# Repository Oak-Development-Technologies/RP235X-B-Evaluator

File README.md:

<image src="Images/RP235X-B_Rendering.png">
# RP235X-B-Evaluator
Open source repository for storing the files for the RP235X-B Evaluator, an RP235X-B Evaluation board.

### Schematic

Here's the first page of the schematic:

<image src="Images/RP235X_FPGA.svg">

### Find the full PDF of the Schematic here:

[PDF Schematic Here](RP235X_FPGA.pdf)

Mind the name of the files, there is plans to eventually add an FPGA add on board for this. Stay tuned! :)

More Coming Soon!

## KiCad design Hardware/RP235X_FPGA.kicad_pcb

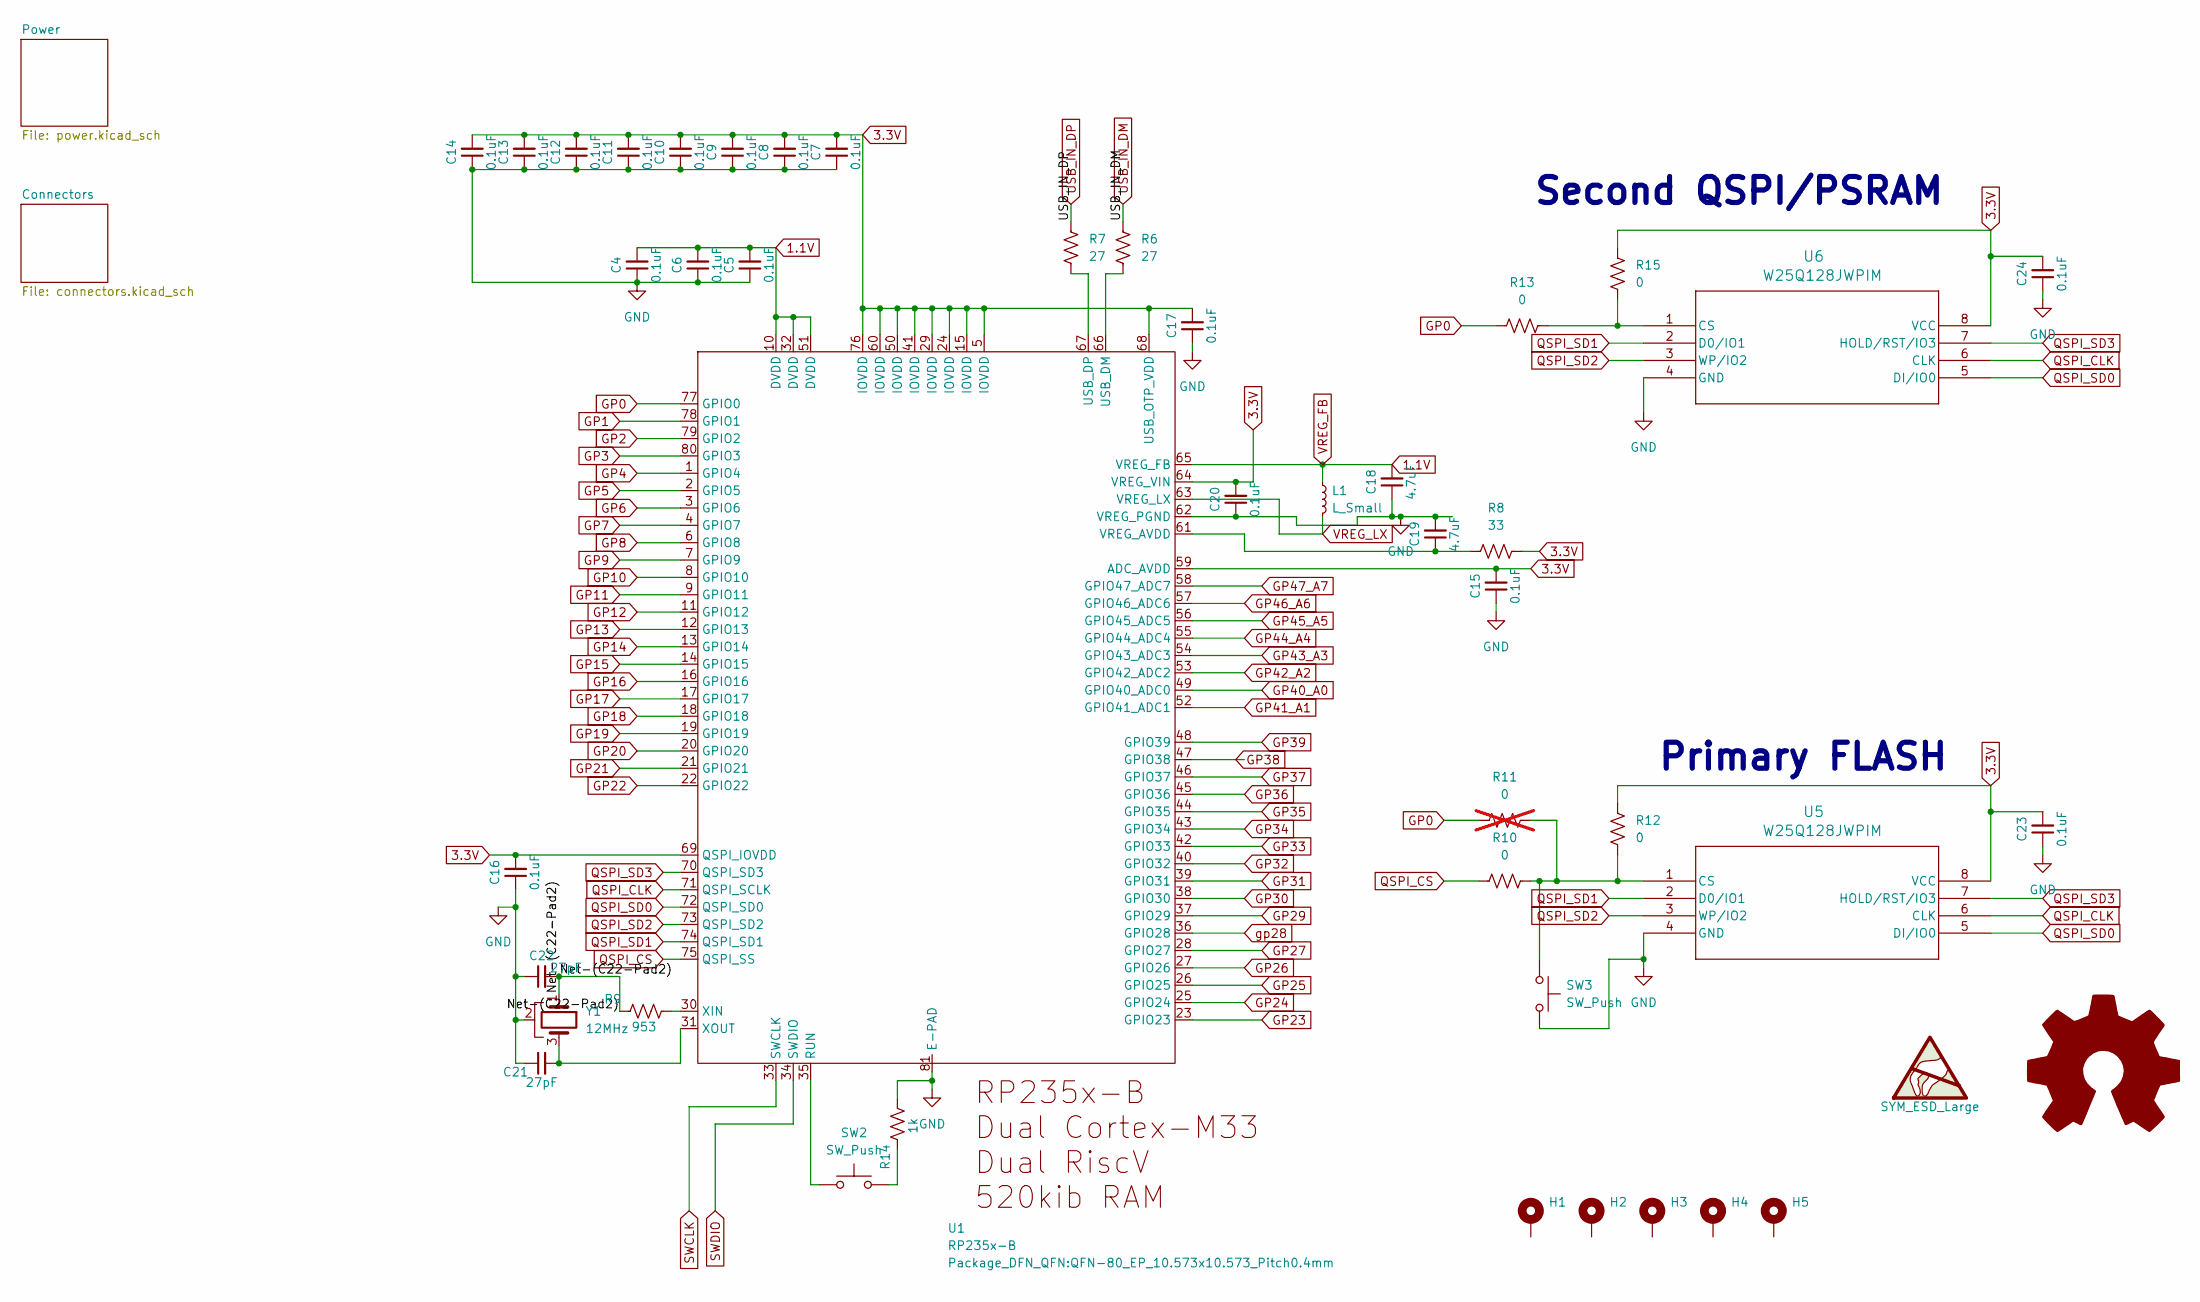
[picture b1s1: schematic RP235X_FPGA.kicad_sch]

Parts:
C4, C5, C6, C7, C8, C9, C10, C11, C12, C13, C14, C15, C16, C17, C20, C23, C24: 0.1uF; C_0402_1005Metric
C18, C19: 4.7uF; C_0402_1005Metric
C21, C22: 27pF; C_0402_1005Metric
H1, H2, H3, H4: MountingHole_Pad; MountingHole_2.5mm_Pad_TopBottom
H5: MountingHole_Pad; KiCad-Logo2_5mm_SilkScreen
L1: L_Small; L_Wurth_WE-LQSH-3012
R6, R7: 27; R_0402_1005Metric
R8: 33; R_0402_1005Metric
R9: 953; R_0402_1005Metric
R10, R12, R13, R15: 0; R_0402_1005Metric
R11: 0; R_0402_1005Metric; not fitted
R14: 1k; R_0402_1005Metric
SW2, SW3: SW_Push; SW_SPST_SKQG_WithStem
U1: RP235x-B; QFN-80_EP_10.573x10.573_Pitch0.4mm
U5, U6: W25Q128JWPIM; W25Q128JW_WSON 6x5-mm_WIN
Y1: 12MHz; Crystal_SMD_SeikoEpson_FA238-4Pin_3.2x2.5mm

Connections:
1.1V: C4.2, C5.2, C6.2, C18.2, L1.1, U1.10 (DVDD), U1.32 (DVDD), U1.51 (DVDD), U1.65 (VREG_FB)
3.3V: C7.2, C8.2, C9.2, C10.2, C11.2, C12.2, C13.2, C14.2, C15.2, C16.2, C17.2, C20.2, C23.2, C24.2, R8.2, R12.2, R15.2, U1.5 (IOVDD), U1.15 (IOVDD), U1.24 (IOVDD), U1.29 (IOVDD), U1.41 (IOVDD), U1.50 (IOVDD), U1.59 (ADC_AVDD), U1.60 (IOVDD), U1.64 (VREG_VIN), U1.68 (USB_OTP_VDD), U1.69 (QSPI_IOVDD), U1.76 (IOVDD), U5.8 (VCC), U6.8 (VCC); also elsewhere on the board
/Net-(C22-Pad2): C22.2, R9.1, Y1.1
GND: C4.1, C5.1, C6.1, C7.1, C8.1, C9.1, C10.1, C11.1, C12.1, C13.1, C14.1, C15.1, C16.1, C17.1, C18.1, C19.2, C20.1, C21.1, C22.1, C23.1, C24.1, R14.2, SW3.2, U1.62 (VREG_PGND), U1.81 (E-PAD), U5.4 (GND), U6.4 (GND), Y1.2; also elsewhere on the board
GP0: R11.1, R13.1, U1.77 (GPIO0); also elsewhere on the board
GP1: U1.78 (GPIO1); also elsewhere on the board
GP2: U1.79 (GPIO2); also elsewhere on the board
GP3: U1.80 (GPIO3); also elsewhere on the board
GP4: U1.1 (GPIO4); also elsewhere on the board
GP5: U1.2 (GPIO5); also elsewhere on the board
GP6: U1.3 (GPIO6); also elsewhere on the board
GP7: U1.4 (GPIO7); also elsewhere on the board
GP8: U1.6 (GPIO8); also elsewhere on the board
GP9: U1.7 (GPIO9); also elsewhere on the board
GP10: U1.8 (GPIO10); also elsewhere on the board
GP11: U1.9 (GPIO11); also elsewhere on the board
GP12: U1.11 (GPIO12); also elsewhere on the board
GP13: U1.12 (GPIO13); also elsewhere on the board
GP14: U1.13 (GPIO14); also elsewhere on the board
GP15: U1.14 (GPIO15); also elsewhere on the board
GP16: U1.16 (GPIO16); also elsewhere on the board
GP17: U1.17 (GPIO17); also elsewhere on the board
GP18: U1.18 (GPIO18); also elsewhere on the board
GP19: U1.19 (GPIO19); also elsewhere on the board
GP20: U1.20 (GPIO20); also elsewhere on the board
GP21: U1.21 (GPIO21); also elsewhere on the board
GP22: U1.22 (GPIO22); also elsewhere on the board
GP23: U1.23 (GPIO23); also elsewhere on the board
GP24: U1.25 (GPIO24); also elsewhere on the board
GP25: U1.26 (GPIO25); also elsewhere on the board
GP26: U1.27 (GPIO26); also elsewhere on the board
GP27: U1.28 (GPIO27); also elsewhere on the board
GP29: U1.37 (GPIO29); also elsewhere on the board
GP30: U1.38 (GPIO30); also elsewhere on the board
GP31: U1.39 (GPIO31); also elsewhere on the board
GP32: U1.40 (GPIO32); also elsewhere on the board
GP33: U1.42 (GPIO33); also elsewhere on the board
GP34: U1.43 (GPIO34); also elsewhere on the board
GP35: U1.44 (GPIO35); also elsewhere on the board
GP36: U1.45 (GPIO36); also elsewhere on the board
GP37: U1.46 (GPIO37); also elsewhere on the board
GP38: U1.47 (GPIO38); also elsewhere on the board
GP39: U1.48 (GPIO39); also elsewhere on the board
GP40_A0: U1.49 (GPIO40_ADC0); also elsewhere on the board
GP41_A1: U1.52 (GPIO41_ADC1); also elsewhere on the board
GP42_A2: U1.53 (GPIO42_ADC2); also elsewhere on the board
GP43_A3: U1.54 (GPIO43_ADC3); also elsewhere on the board
GP44_A4: U1.55 (GPIO44_ADC4); also elsewhere on the board
GP45_A5: U1.56 (GPIO45_ADC5); also elsewhere on the board
GP46_A6: U1.57 (GPIO46_ADC6); also elsewhere on the board
GP47_A7: U1.58 (GPIO47_ADC7); also elsewhere on the board
unnamed: R14.1, SW2.2
unnamed: SW2.1, U1.35 (RUN)
unnamed: R6.2, U1.66 (USB_DM)
unnamed: R7.2, U1.67 (USB_DP)
unnamed: C19.1, R8.1, U1.61 (VREG_AVDD)
unnamed: R9.2, U1.30 (XIN)
unnamed: C21.2, U1.31 (XOUT), Y1.3
unnamed: R10.2, R11.2, R12.1, SW3.1, U5.1 (CS)
unnamed: R13.2, R15.1, U6.1 (CS)
QSPI_CLK: U1.71 (QSPI_SCLK), U5.6 (CLK), U6.6 (CLK)
QSPI_CS: R10.1, U1.75 (QSPI_SS)
QSPI_SD0: U1.72 (QSPI_SD0), U5.5 (DI/IO0), U6.5 (DI/IO0)
QSPI_SD1: U1.74 (QSPI_SD1), U5.2 (D0/IO1), U6.2 (D0/IO1)
QSPI_SD2: U1.73 (QSPI_SD2), U5.3 (WP/IO2), U6.3 (WP/IO2)
QSPI_SD3: U1.70 (QSPI_SD3), U5.7 (HOLD/RST/IO3), U6.7 (HOLD/RST/IO3)
SWCLK: U1.33 (SWCLK); also elsewhere on the board
SWDIO: U1.34 (SWDIO); also elsewhere on the board
USB_IN_DM: R6.1; also elsewhere on the board
USB_IN_DP: R7.1; also elsewhere on the board
VREG_LX: L1.2, U1.63 (VREG_LX)
gp28: U1.36 (GPIO28); also elsewhere on the board

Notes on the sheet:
Second QSPI/PSRAM
Primary FLASH

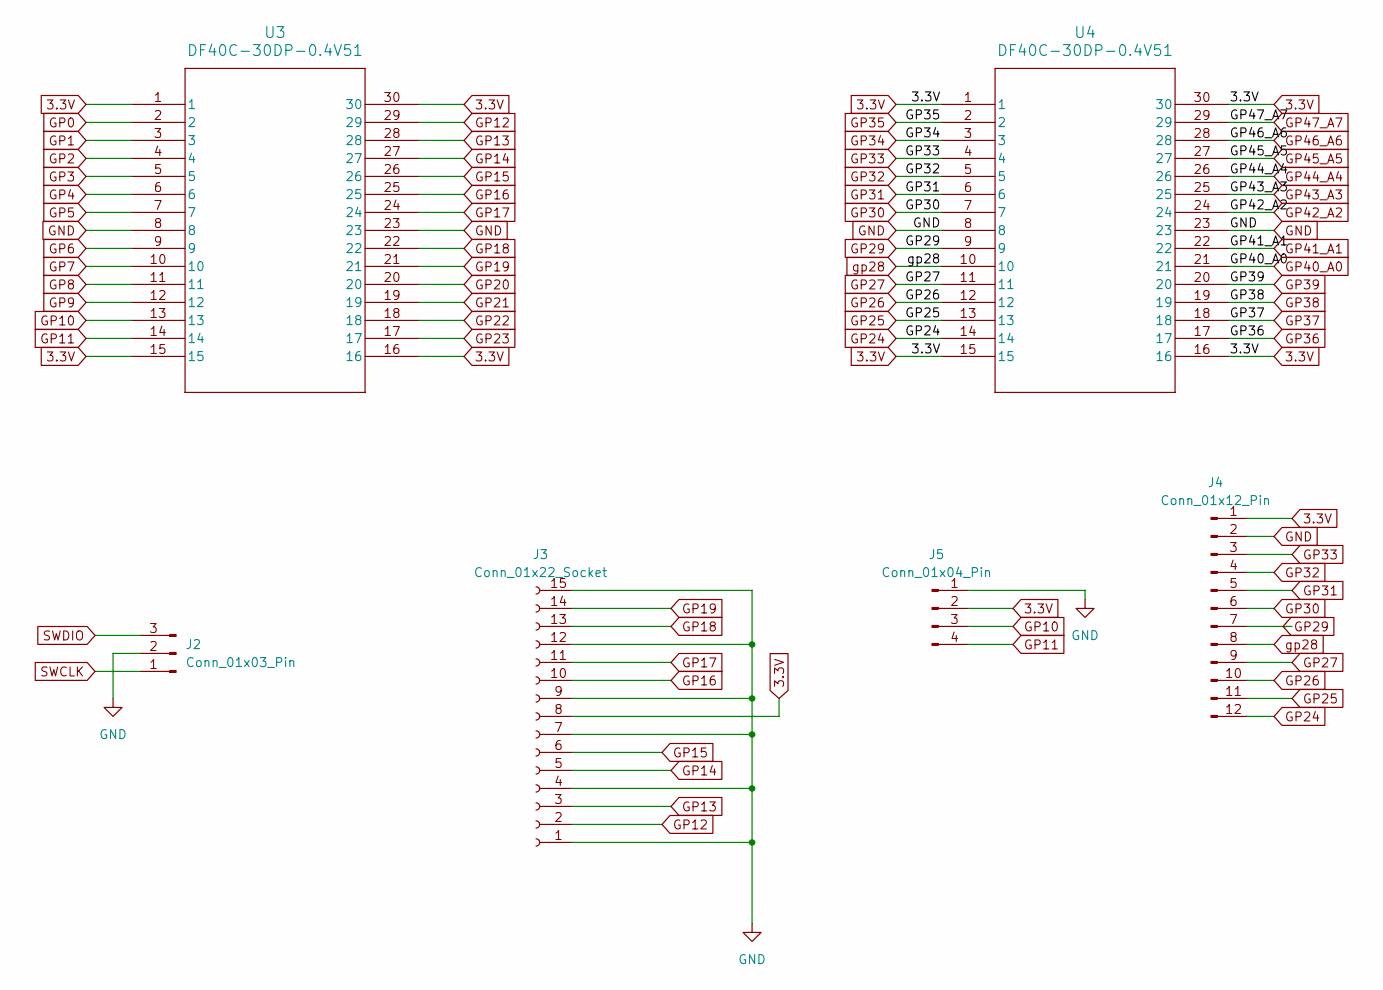
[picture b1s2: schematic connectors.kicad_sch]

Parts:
J2: Conn_01x03_Pin; JST_SH_SM03B-SRSS-TB_1x03-1MP_P1.00mm_Horizontal
J3: Conn_01x22_Socket; Hirose_FH12-15S-0.5SH_1x15-1MP_P0.50mm_Horizontal
J4: Conn_01x12_Pin; PinHeader_1x12_P2.54mm_Horizontal
J5: Conn_01x04_Pin; JST_SH_BM04B-SRSS-TB_1x04-1MP_P1.00mm_Vertical
U3, U4: DF40C-30DP-0.4V51; SOIC_0DP-0.4V51_HIR

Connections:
3.3V: J3.8, J4.1, J5.2, U3.1, U3.15, U3.16, U3.30, U4.1, U4.15, U4.16, U4.30; also elsewhere on the board
GND: J2.2, J3.1, J3.4, J3.7, J3.9, J3.12, J3.15, J4.2, J5.1, U3.8, U3.23, U4.8, U4.23; also elsewhere on the board
GP0: U3.2; also elsewhere on the board
GP1: U3.3; also elsewhere on the board
GP2: U3.4; also elsewhere on the board
GP3: U3.5; also elsewhere on the board
GP4: U3.6; also elsewhere on the board
GP5: U3.7; also elsewhere on the board
GP6: U3.9; also elsewhere on the board
GP7: U3.10; also elsewhere on the board
GP8: U3.11; also elsewhere on the board
GP9: U3.12; also elsewhere on the board
GP10: J5.3, U3.13; also elsewhere on the board
GP11: J5.4, U3.14; also elsewhere on the board
GP12: J3.2, U3.29; also elsewhere on the board
GP13: J3.3, U3.28; also elsewhere on the board
GP14: J3.5, U3.27; also elsewhere on the board
GP15: J3.6, U3.26; also elsewhere on the board
GP16: J3.10, U3.25; also elsewhere on the board
GP17: J3.11, U3.24; also elsewhere on the board
GP18: J3.13, U3.22; also elsewhere on the board
GP19: J3.14, U3.21; also elsewhere on the board
GP20: U3.20; also elsewhere on the board
GP21: U3.19; also elsewhere on the board
GP22: U3.18; also elsewhere on the board
GP23: U3.17; also elsewhere on the board
GP24: J4.12, U4.14; also elsewhere on the board
GP25: J4.11, U4.13; also elsewhere on the board
GP26: J4.10, U4.12; also elsewhere on the board
GP27: J4.9, U4.11; also elsewhere on the board
GP29: J4.7, U4.9; also elsewhere on the board
GP30: J4.6, U4.7; also elsewhere on the board
GP31: J4.5, U4.6; also elsewhere on the board
GP32: J4.4, U4.5; also elsewhere on the board
GP33: J4.3, U4.4; also elsewhere on the board
GP34: U4.3; also elsewhere on the board
GP35: U4.2; also elsewhere on the board
GP36: U4.17; also elsewhere on the board
GP37: U4.18; also elsewhere on the board
GP38: U4.19; also elsewhere on the board
GP39: U4.20; also elsewhere on the board
GP40_A0: U4.21; also elsewhere on the board
GP41_A1: U4.22; also elsewhere on the board
GP42_A2: U4.24; also elsewhere on the board
GP43_A3: U4.25; also elsewhere on the board
GP44_A4: U4.26; also elsewhere on the board
GP45_A5: U4.27; also elsewhere on the board
GP46_A6: U4.28; also elsewhere on the board
GP47_A7: U4.29; also elsewhere on the board
SWCLK: J2.1; also elsewhere on the board
SWDIO: J2.3; also elsewhere on the board
gp28: J4.8, U4.10; also elsewhere on the board

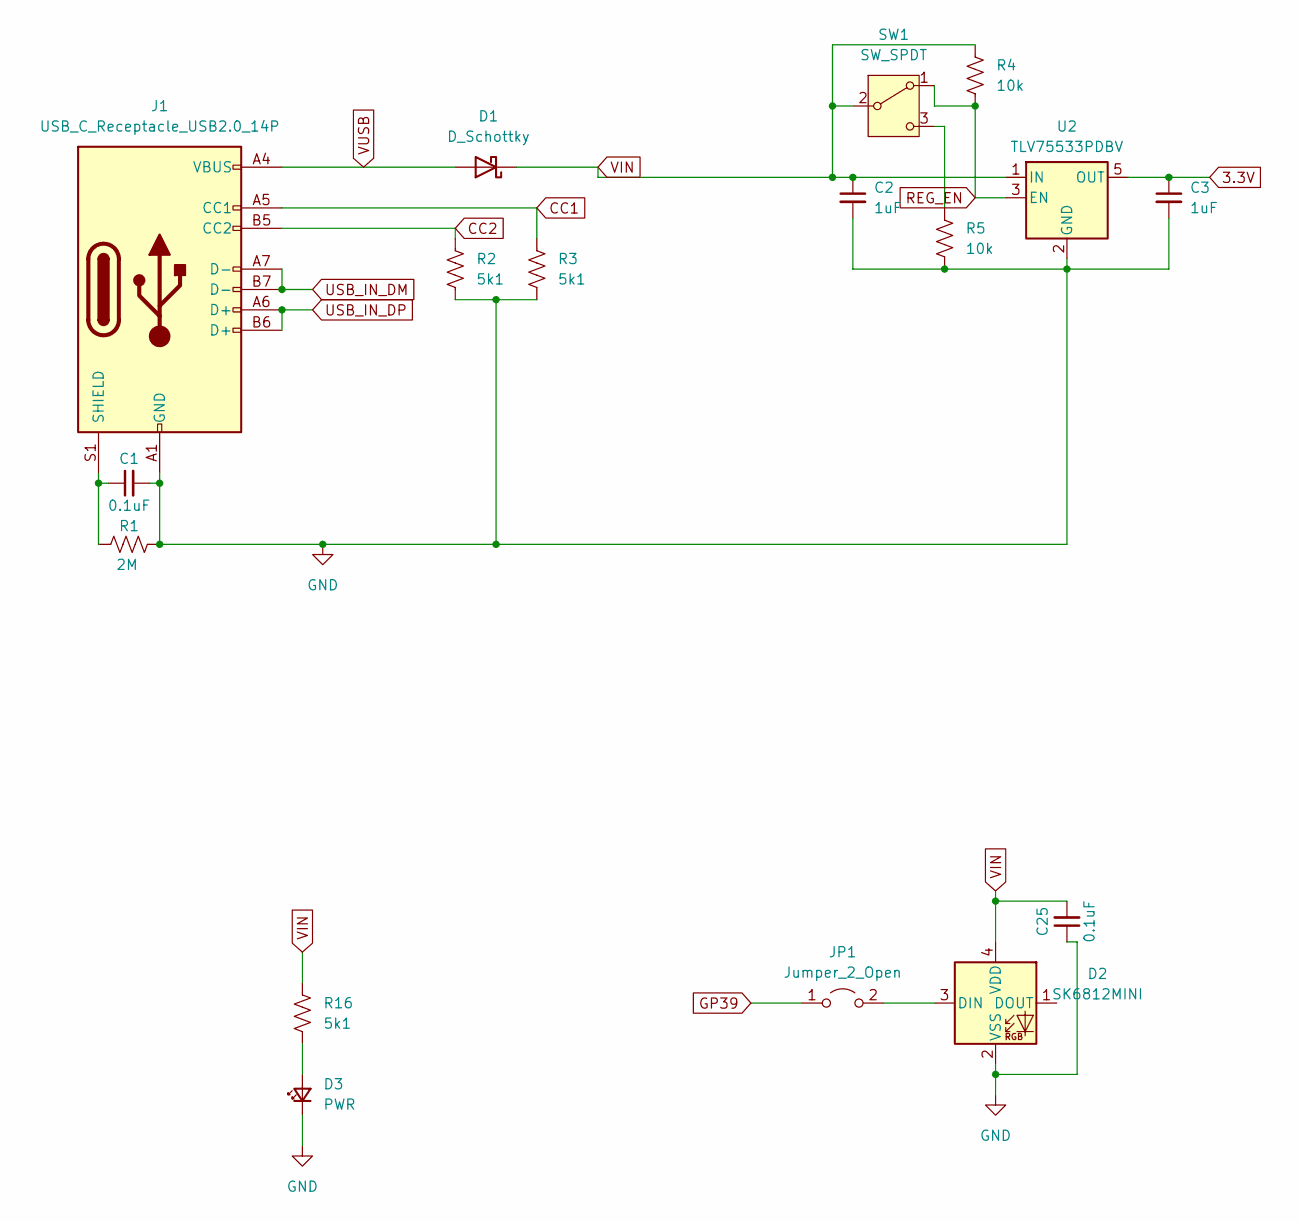
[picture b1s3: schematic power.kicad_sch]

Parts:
C1, C25: 0.1uF; C_0402_1005Metric
C2, C3: 1uF; C_0805_2012Metric
D1: D_Schottky; D_SOD-123
D2: SK6812MINI; LED_SK6812MINI_PLCC4_3.5x3.5mm_P1.75mm
D3: PWR; LED_0603_1608Metric
J1: USB_C_Receptacle_USB2.0_14P; USB_C_Receptacle_GCT_USB4105-xx-A_16P_TopMnt_Horizontal
JP1: Jumper_2_Open; SolderJumper-2_P1.3mm_Open_RoundedPad1.0x1.5mm
R1: 2M; R_0402_1005Metric
R2, R3, R16: 5k1; R_0402_1005Metric
R4, R5: 10k; R_0402_1005Metric
SW1: SW_SPDT; SW_SPDT_CK_JS102011SAQN
U2: TLV75533PDBV; SOT-23-5

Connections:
3.3V: C3.1, U2.5 (OUT); also elsewhere on the board
CC1: J1.A5 (CC1), R3.2
CC2: J1.B5 (CC2), R2.2
GND: C1.2, C2.2, C3.2, C25.1, D2.2 (VSS), D3.1 (K), J1.A1 (GND), J1.A12 (GND), J1.B1 (GND), J1.B12 (GND), R1.2, R2.1, R3.1, R5.2, U2.2 (GND); also elsewhere on the board
GP39: JP1.1 (A); also elsewhere on the board
unnamed: D2.3 (DIN), JP1.2 (B)
unnamed: D3.2 (A), R16.2
unnamed: C1.1, J1.S1 (SHIELD), R1.1
unnamed: R5.1, SW1.3 (C)
REG_EN: R4.2, SW1.1 (A), U2.3 (EN)
USB_IN_DM: J1.A7 (D-), J1.B7 (D-); also elsewhere on the board
USB_IN_DP: J1.A6 (D+), J1.B6 (D+); also elsewhere on the board
VIN: C2.1, C25.2, D1.1 (K), D2.4 (VDD), R4.1, R16.1, SW1.2 (B), U2.1 (IN)
VUSB: D1.2 (A), J1.A4 (VBUS), J1.A9 (VBUS), J1.B4 (VBUS), J1.B9 (VBUS)

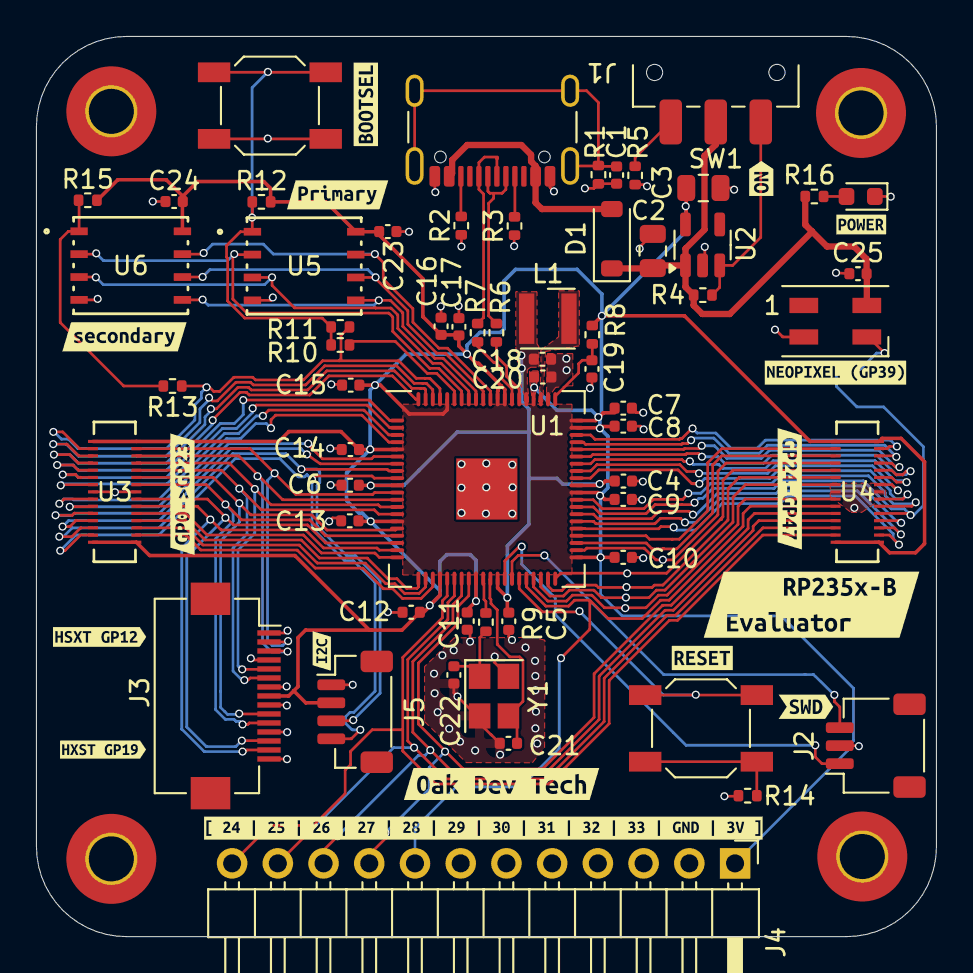
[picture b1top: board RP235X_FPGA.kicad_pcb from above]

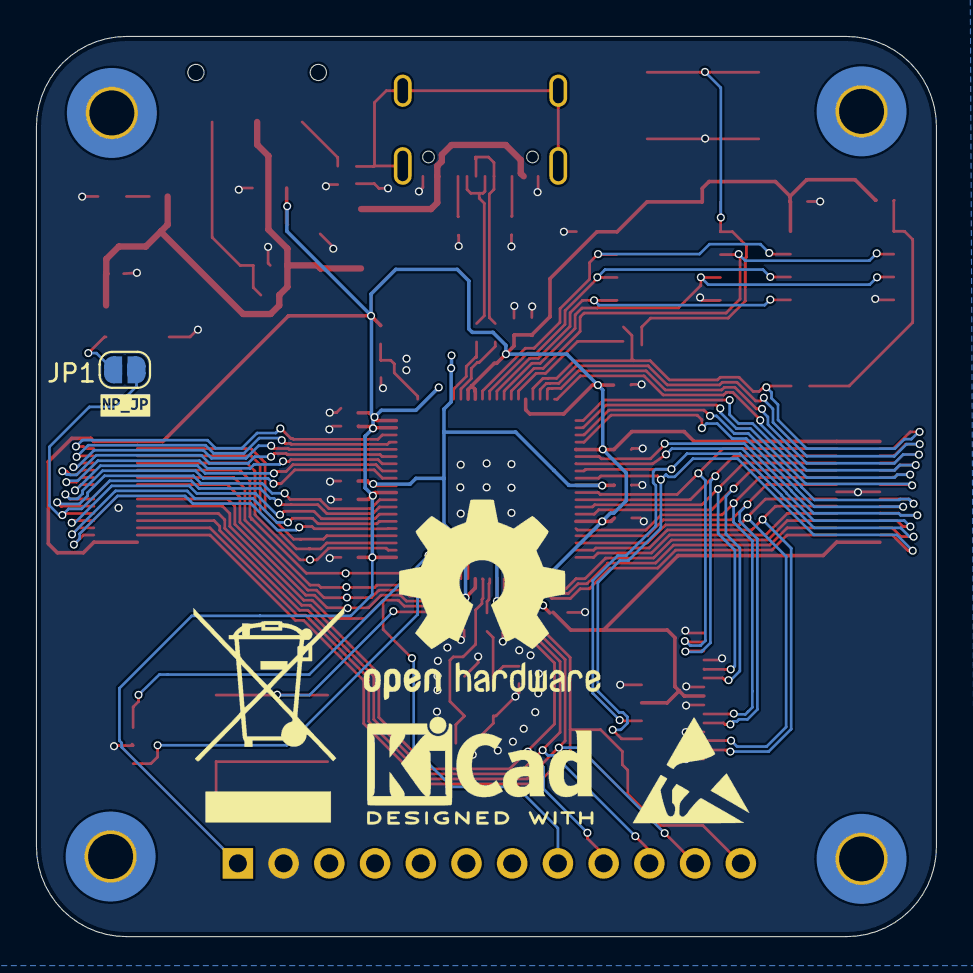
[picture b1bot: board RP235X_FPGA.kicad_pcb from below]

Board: 4 copper layers, 50.0 x 50.0 mm, 83 parts (3 on the bottom side), 81 nets.

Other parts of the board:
kibuzzard-66B63CDC: G***; kibuzzard-66B63CDC
kibuzzard-66B63CFB: G***; kibuzzard-66B63CFB
kibuzzard-66B63D0B: G***; kibuzzard-66B63D0B
kibuzzard-66B63D2E: G***; kibuzzard-66B63D2E
kibuzzard-66B63D3D: G***; kibuzzard-66B63D3D
kibuzzard-66B63D82: G***; kibuzzard-66B63D82
kibuzzard-66B63D92: G***; kibuzzard-66B63D92
kibuzzard-66B63DAC: G***; kibuzzard-66B63DAC
kibuzzard-66B650E6: G***; kibuzzard-66B650E6
kibuzzard-66B694FA: G***; kibuzzard-66B694FA
kibuzzard-66B695F4: G***; kibuzzard-66B695F4
kibuzzard-66B6615E: G***; kibuzzard-66B6615E
kibuzzard-66B6616B: G***; kibuzzard-66B6616B
kibuzzard-66B65027: G***; kibuzzard-66B65027
kibuzzard-66B65044: G***; kibuzzard-66B65044
kibuzzard-66B66391: G***; kibuzzard-66B66391
kibuzzard-66B69604: G***; kibuzzard-66B69604

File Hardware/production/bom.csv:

Designator,Footprint,Quantity,Value,LCSC Part #
"C1, C10, C11, C12, C13, C14, C15, C16, C17, C20, C23, C24, C25, C4, C5, C6, C7, C8, C9",0402,19,0.1uF,
"C18, C19",0402,2,4.7uF,
"C2, C3",0805,2,1uF,
"C21, C22",0402,2,27pF,
D1,D_SOD-123,1,D_Schottky,
D2,LED_SK6812MINI_PLCC4_3.5x3.5mm_P1.75mm,1,SK6812MINI,
D3,0603,1,PWR,
"H1, H2, H3, H4",MountingHole_2.5mm_Pad_TopBottom,4,MountingHole_Pad,
J1,USB_C_Receptacle_GCT_USB4105-xx-A_16P_TopMnt_Horizontal,1,USB_C_Receptacle_USB2.0_14P,
J2,JST_SH_SM03B-SRSS-TB_1x03-1MP_P1.00mm_Horizontal,1,Conn_01x03_Pin,
J3,Hirose_FH12-15S-0.5SH_1x15-1MP_P0.50mm_Horizontal,1,Conn_01x22_Socket,
J4,PinHeader_1x12_P2.54mm_Horizontal,1,Conn_01x12_Pin,
J5,JST_SH_BM04B-SRSS-TB_1x04-1MP_P1.00mm_Vertical,1,Conn_01x04_Pin,
JP1,SolderJumper-2_P1.3mm_Open_RoundedPad1.0x1.5mm,1,Jumper_2_Open,
L1,L_Wurth_WE-LQSH-3012,1,L_Small,
R1,0402,1,2M,
"R10, R11, R12, R13, R15",0402,5,0,
R14,0402,1,1k,
"R16, R2, R3",0402,3,5k1,
"R4, R5",0402,2,10k,
"R6, R7",0402,2,27,
R8,0402,1,33,
R9,0402,1,953,
SW1,SW_SPDT_CK_JS102011SAQN,1,SW_SPDT,
"SW2, SW3",SW_SPST_SKQG_WithStem,2,SW_Push,
U1,QFN-80_EP_10.573x10.573_Pitch0.4mm,1,RP235x-B,
U2,SOT-23-5,1,TLV75533PDBV,
"U3, U4",SOIC_0DP-0.4V51_HIR,2,DF40C-30DP-0.4V51,
"U5, U6",W25Q128JW_WSON 6x5-mm_WIN,2,W25Q128JWPIM,
Y1,Crystal_SMD_SeikoEpson_FA238-4Pin_3.2x2.5mm,1,12MHz,

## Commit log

2024-08-09 add some basic stuff to the repo
2024-08-09 Create LICENSE
    CERN OHL V2 License
2024-08-12 Add PDF of schematic
2024-08-12 Add image of first page of sch
2024-08-12 update image to use white background
2024-08-12 one more try on sch image
